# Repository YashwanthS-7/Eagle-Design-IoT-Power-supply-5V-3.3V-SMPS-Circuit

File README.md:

# Eagle-Design-IoT-Power-supply-5V-3.3V-SMPS-Circuit
Nowadays, the IoT (Internet of Things) uses various WIFI-based processors like NodeMCU, ESP32, and ESP12E, etc. which operate on 5V or 3.3V. These modules are highly compact and hence to power these boards, it makes sense to use smaller SMPS circuits that can go on the same board, instead of using a separate SMPS circuit.

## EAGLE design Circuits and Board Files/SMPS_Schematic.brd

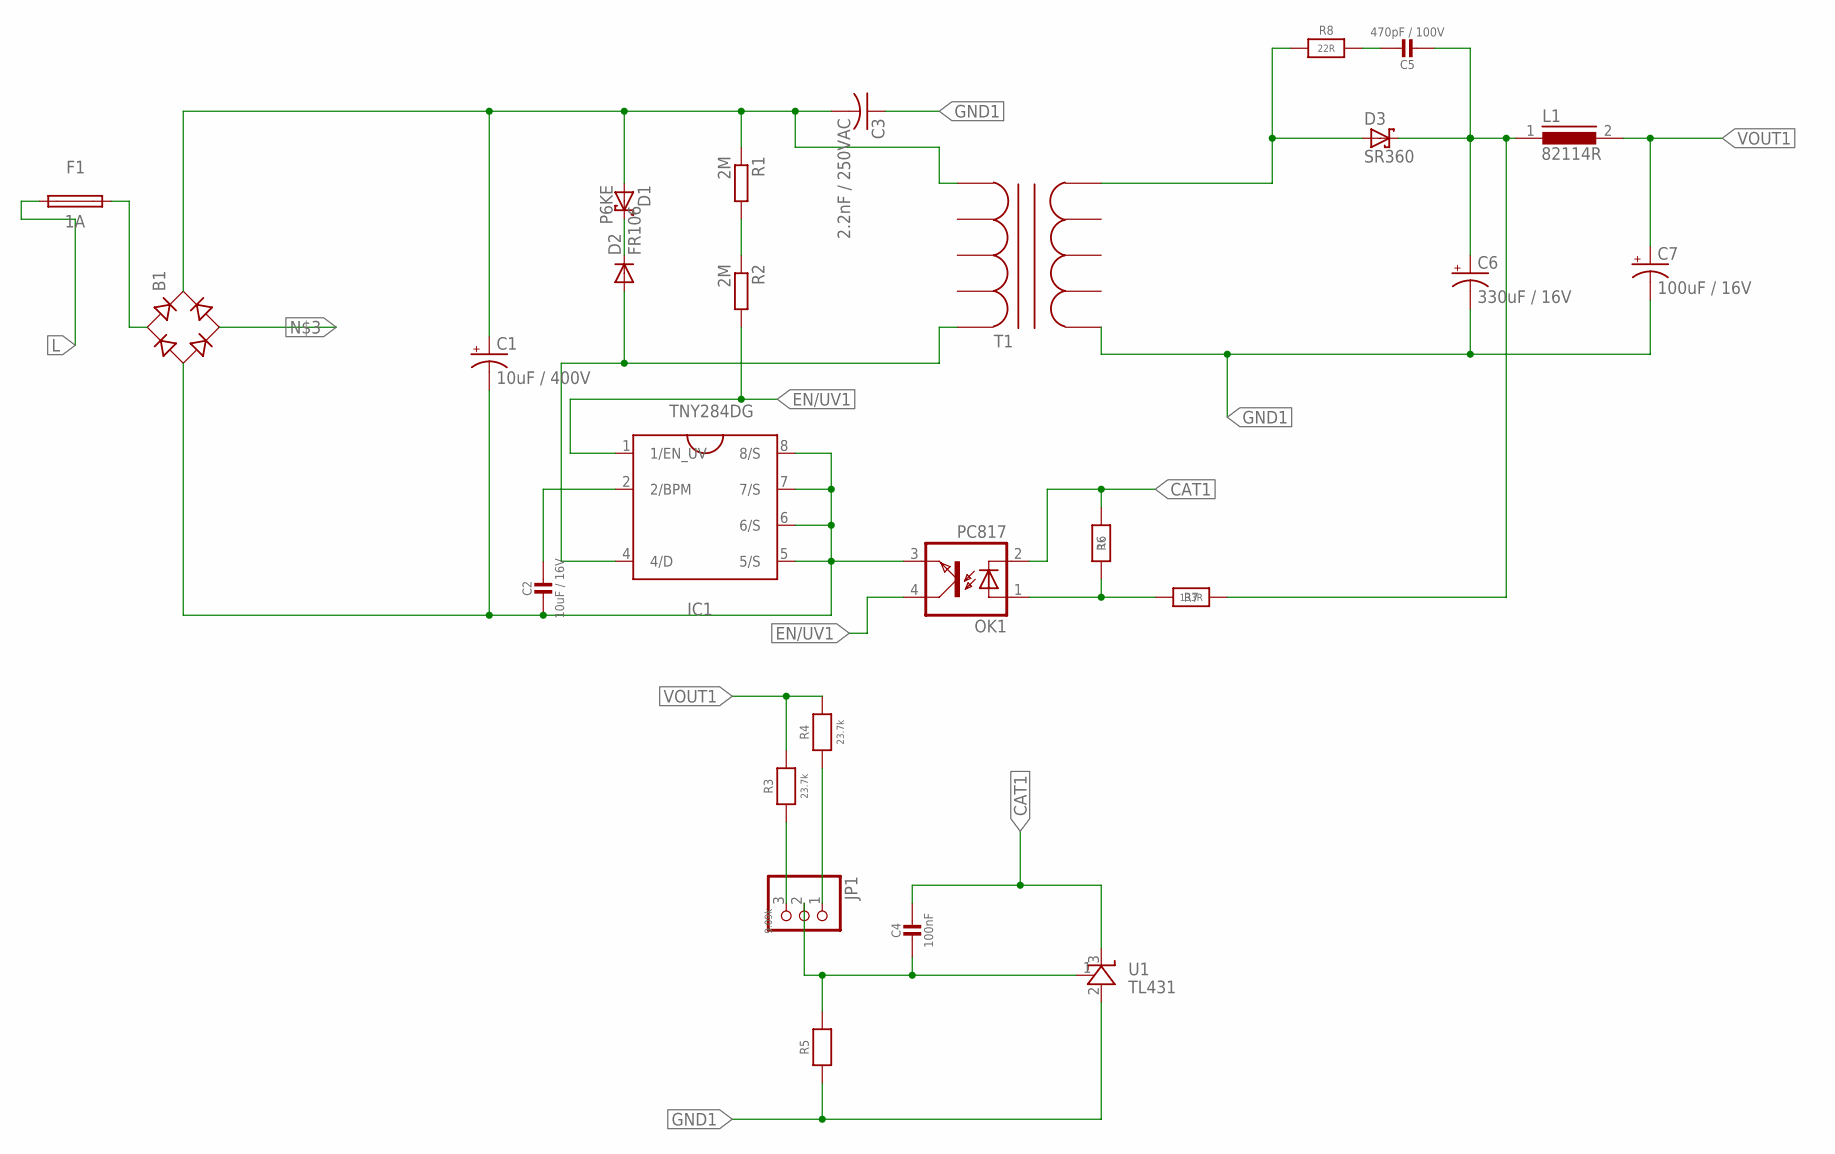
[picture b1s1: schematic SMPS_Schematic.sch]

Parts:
B1: B-DIL
C1: 10uF / 400V; E5-10,5
C2: 10uF / 16V; 0805-NO
C3: 2.2nF / 250VAC; C075-032X103
C4: 100nF; 0805-NO
C5: 470pF / 100V; 0805-NO
C6: 330uF / 16V; E3,5-8
C7: 100uF / 16V; E2,5-7
D1: P6KE; CB417-15
D2: FR106; DO41-10
D3: SR360; C4111-15
F1: 1A; TR5
IC1: TNY284DG; SO8-C(D_PACKAGE)
JP1: PINHD-1X3; 1X03
L1: 82114R
OK1: PC817; DIL04
R1, R2: 2M; M1206
R3, R4: 23.7k; 0805-NO
R5: 9.09k; 0805-NO
R6: 1k; 0805-NO
R7: 133R; 0805-NO
R8: 22R; 0805-NO
T1: TRANSFORMER_EE16; EE16
U1: TL431; TO-92

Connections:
AN1: C5.2, C6.+, D3.C, L1.1, R7.2
BP/M: C2.1, IC1.2 (2/BPM)
CAT1: C4.1, OK1.2 (C), R6.1, U1.3 (C)
DRAIN: D2.A, IC1.4 (4/D), T1.P$5
EN/UV1: IC1.1 (1/EN_UV), OK1.4 (COL), R2.2
GND: C7.+, L1.2, R3.2, R4.2
GND1: C3.1, C6.-, C7.-, R5.1, T1.P$6, U1.2 (A)
HV+: B1.+, C1.+, C3.2, D1.A, R1.1, T1.P$1
L: F1.P$1 (1)
N: B1.AC2
unnamed: JP1.1, R4.1
unnamed: JP1.3, R3.1
unnamed: OK1.1 (A), R6.2, R7.1
unnamed: D1.C, D2.C
unnamed: C5.1, R8.2
unnamed: R1.2, R2.1
unnamed: C4.2, JP1.2, R5.2, U1.1 (REF)
unnamed: B1.AC1, F1.P$2 (2)
SEC1: D3.A, R8.1, T1.P$10
SOURCE: B1.-, C1.-, C2.2, IC1.5 (5/S), IC1.6 (6/S), IC1.7 (7/S), IC1.8 (8/S), OK1.3 (EMIT)

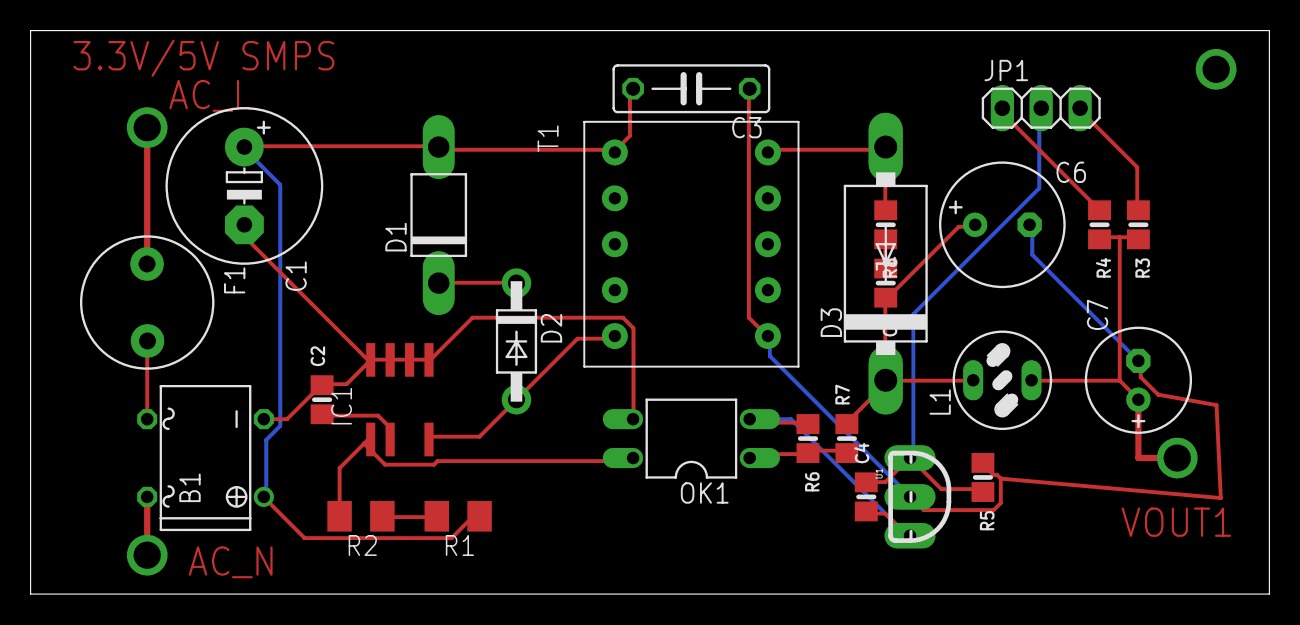
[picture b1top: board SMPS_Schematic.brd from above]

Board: 2 copper layers, 81.0 x 36.8 mm, 26 parts (0 on the bottom side), 18 nets.

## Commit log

2024-12-10 created a folder

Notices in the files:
parts and their libraries:
microbuilder: This work is placed in the public domain, and may be freely used for commercial and non-commercial work with the following conditions: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
